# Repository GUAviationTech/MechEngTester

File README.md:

### Tester Project for 2502ENG Mech Eng

Used to test motors (through an L298N) and servos (direct).

Motors will run and servos will rotate when the respective button is pressed. 360deg servos will constantly rotate, but will change direction when the button is pressed. 

Ensure the battery is set around 6-8V to not blow out the servos.

I have also included a mounting bracket that sits on top of the existing battery pack.

# PCB

# BOM

I just used whatever was on hand, nothing is critical

- WAGO 2601-3104 x2
- LED x2 (I have used green LEDs, but red or clear might be easier to see)
- 12mm pushbutton switch x2
- 10k Resistor x4
- 470uF electrolytic capacitor x1 (Anything around 500uF should be fine)
- Long male header pins

# Assembly

1. Solder components. Header pins need enough depth to mount to the Leonardo, but also enough height to attach leads.

2. Attach to Leonardo. 

3. Set voltage

4. Attach servo and L298N board

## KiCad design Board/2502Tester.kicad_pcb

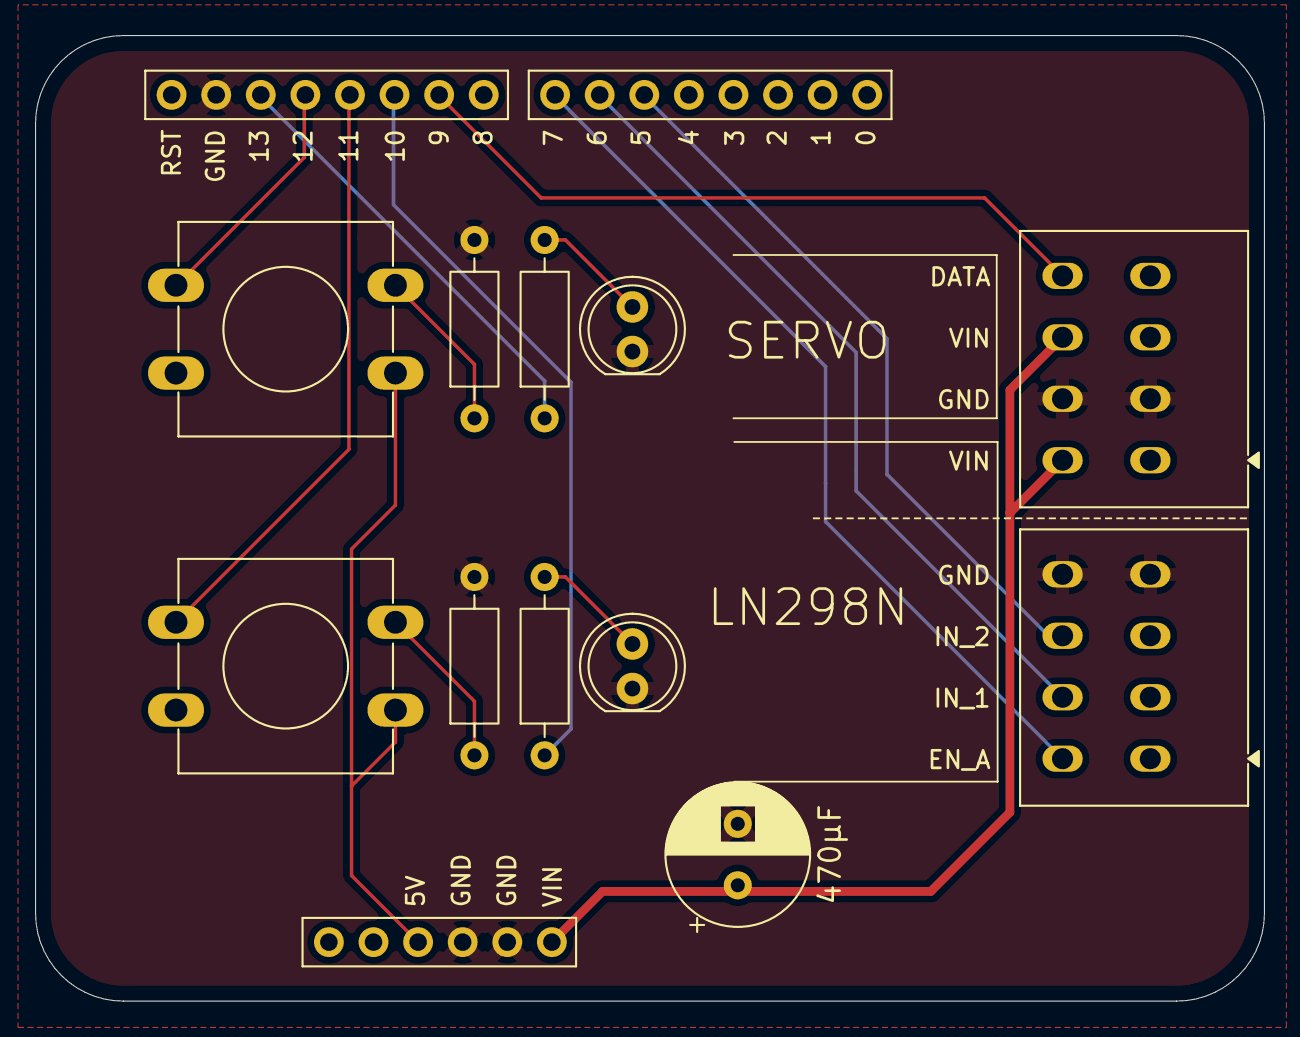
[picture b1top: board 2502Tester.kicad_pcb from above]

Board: 2 copper layers, 70.0 x 55.0 mm, 14 parts (0 on the bottom side), 13 nets.

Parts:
C1: 470μF; CP_Radial_D8.0mm_P3.50mm
D3, D4: LED_Small; LED_D5.0mm_Clear
J1_STEPPER1: STEPPER; TerminalBlock_WAGO_2601-3104_1x04_P3.50mm_Vertical
J2_SERVO1: SERVO; TerminalBlock_WAGO_2601-3104_1x04_P3.50mm_Vertical
J7: LeoPins8; PinHeader_1x08_P2.54mm_Vertical
J8: LeoPins0; PinHeader_1x08_P2.54mm_Vertical
J9: Leo_Power; PinHeader_1x06_P2.54mm_Vertical
R2, R3, R4, R5: 10k; R_Axial_DIN0207_L6.3mm_D2.5mm_P10.16mm_Horizontal
SW1: SW_SERVO; SW_PUSH-12mm
SW2: SW_STEPPER; SW_PUSH-12mm

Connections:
+5V: J9.3 (Pin_3_3), SW1.1, SW2.1
/SERVO: J2_SERVO1.4, J7.2
/STEPPER_EN_A: J1_STEPPER1.1, J8.8
/STEPPER_IN_1: J1_STEPPER1.2, J8.7
/STEPPER_IN_2: J1_STEPPER1.3, J8.6
/VIN: C1.1, J2_SERVO1.1, J2_SERVO1.3, J9.6 (Pin_2_2)
GND: C1.2, D3.1 (K), D4.1 (K), J1_STEPPER1.4, J2_SERVO1.2, J7.7, J9.4 (Pin_4_4), J9.5 (Pin_1_1), R4.2, R5.2
LED_SERVO: J7.6, R2.1
LED_STEPPER: J7.3, R3.1
unnamed: D3.2 (A), R2.2
unnamed: D4.2 (A), R3.2
SW_SERVO: J7.5, R4.1, SW1.2
SW_STEPPER: J7.4, R5.1, SW2.2

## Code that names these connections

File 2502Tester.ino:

// #include <stdio.h>
#include <Servo.h>
#include <Stepper.h>

int PIN_LED_SERVO = 13;
int PIN_LED_STEPPER = 10;
int PIN_BTN_SERVO = 12;
int PIN_BTN_STEPPER = 11;

int PIN_SERVO = 9;

int PIN_STEPPER_EN_A = 5;
int PIN_STEPPER_IN_1 = 6;
int PIN_STEPPER_IN_2 = 7;

Servo servo;

int STEPPER_TEST_VALUE = 180;

void setup() {

  Serial.begin(9600);

  // Buttons and lights

  pinMode(PIN_LED_SERVO, OUTPUT);
  pinMode(PIN_LED_STEPPER, OUTPUT);
  pinMode(PIN_BTN_SERVO, INPUT);
  pinMode(PIN_BTN_STEPPER, INPUT);

  // pinMode(PIN_SERVO_PWR, OUTPUT);

  // Stepper Motor

  pinMode(PIN_STEPPER_EN_A, OUTPUT);
  pinMode(PIN_STEPPER_IN_1, OUTPUT);
  pinMode(PIN_STEPPER_IN_2, OUTPUT);

  digitalWrite(PIN_STEPPER_IN_1, LOW);
  digitalWrite(PIN_STEPPER_IN_2, HIGH);
  analogWrite(PIN_STEPPER_EN_A, 0);

  // Servo

  servo.attach(PIN_SERVO);
  servo.write(0);
  
  delay(100);

  // Let everything settle and signal all good
  delay(1000);

  digitalWrite(PIN_LED_STEPPER, HIGH);
  digitalWrite(PIN_LED_SERVO, HIGH);
  delay(100);
  digitalWrite(PIN_LED_STEPPER, LOW);
  digitalWrite(PIN_LED_SERVO, LOW);
  delay(100);
  digitalWrite(PIN_LED_STEPPER, HIGH);
  digitalWrite(PIN_LED_SERVO, HIGH);
  delay(100);
  digitalWrite(PIN_LED_STEPPER, LOW);
  digitalWrite(PIN_LED_SERVO, LOW);
  delay(200);

}


void testServo(int start = 0, int stop = 180, int incr = 1, int stepDelay = 5) {
  
  if(Serial){
    Serial.print("Testing servo ");
    Serial.print(start);
    Serial.print(" -> ");
    Serial.print(stop);
    Serial.print("\n");
  }

  int dir = 1;
  dir = (start < stop) ? 1 : -1;

  // digitalWrite(PIN_LED, HIGH);
  if(dir == 1) {
    for(int p = start; p <= stop; p += incr) {
      servo.write(p);
      delay(stepDelay);
    }
  }

  if(dir == -1) {
    for(int p = start; p >= stop; p -= incr) {
      servo.write(p);
      delay(stepDelay);
    }
  }
  
  //servo.detach();

  // digitalWrite(PIN_LED, LOW);
}

void testMotor(int dir = 1, int speed = 255, int duration = 5000) {

  if(Serial) {
    String dirStr = (dir > 0) ? "forwards" : "backwards";
    Serial.print("Running motor ");
    Serial.print(dirStr);
    Serial.print(" for ");
    Serial.print(duration);
    Serial.print("ms\n");
  }

  // digitalWrite(PIN_LED, HIGH);

  if(dir > 0) {
    digitalWrite(PIN_STEPPER_IN_1, HIGH);
    digitalWrite(PIN_STEPPER_IN_2, LOW);
  }

  else {
    digitalWrite(PIN_STEPPER_IN_1, LOW);
    digitalWrite(PIN_STEPPER_IN_2, HIGH);
  }

  // digitalWrite(PIN_LED, HIGH);
  analogWrite(PIN_STEPPER_EN_A, speed);
  delay(duration);
  analogWrite(PIN_STEPPER_EN_A, 0);
  
  // digitalWrite(PIN_LED, LOW);

}

void testMotorAccel(int start = 0, int target = 255, int duration = 5000, int hold = 2000) {

  // Accelerate forwards
  digitalWrite(PIN_STEPPER_IN_1, HIGH);
  digitalWrite(PIN_STEPPER_IN_2, LOW);

  if(Serial)
    Serial.println("Testing acceleration");

  int delayTime = duration / 100;

  // Speed up

  for(int i = 0; i <= 100; i += 1) {
    int value = map(i, 0, 100, start, target);
    // analogWrite(PIN_LED, value);
    analogWrite(PIN_STEPPER_EN_A, value);

    delay(delayTime);
  }

  delay(hold);

  // Slow down

  for(int i = 100; i >= 0; i -= 1) {
    int value = map(i, 0, 100, start, target);
    // analogWrite(PIN_LED, value);
    analogWrite(PIN_STEPPER_EN_A, value);

    delay(delayTime);
  }

}

void loop() {

  // Servo button

  if(digitalRead(PIN_BTN_SERVO)) {
    digitalWrite(PIN_LED_SERVO, HIGH);
    servo.write(STEPPER_TEST_VALUE);
  }

  else {
    digitalWrite(PIN_LED_SERVO, LOW);
    servo.write(0);
  }



  if(digitalRead(PIN_BTN_STEPPER)) {
    digitalWrite(PIN_LED_STEPPER, HIGH);
    // digitalWrite(13, HIGH);

    // digitalWrite(PIN_STEPPER_IN_1, HIGH);
    // digitalWrite(PIN_STEPPER_IN_2, LOW);
    analogWrite(PIN_STEPPER_EN_A, 200);

  }

  else {
    digitalWrite(PIN_LED_STEPPER, LOW);
    // digitalWrite(13, LOW);
    analogWrite(PIN_STEPPER_EN_A, 0);
  }

  delay(100);

  return;

}
